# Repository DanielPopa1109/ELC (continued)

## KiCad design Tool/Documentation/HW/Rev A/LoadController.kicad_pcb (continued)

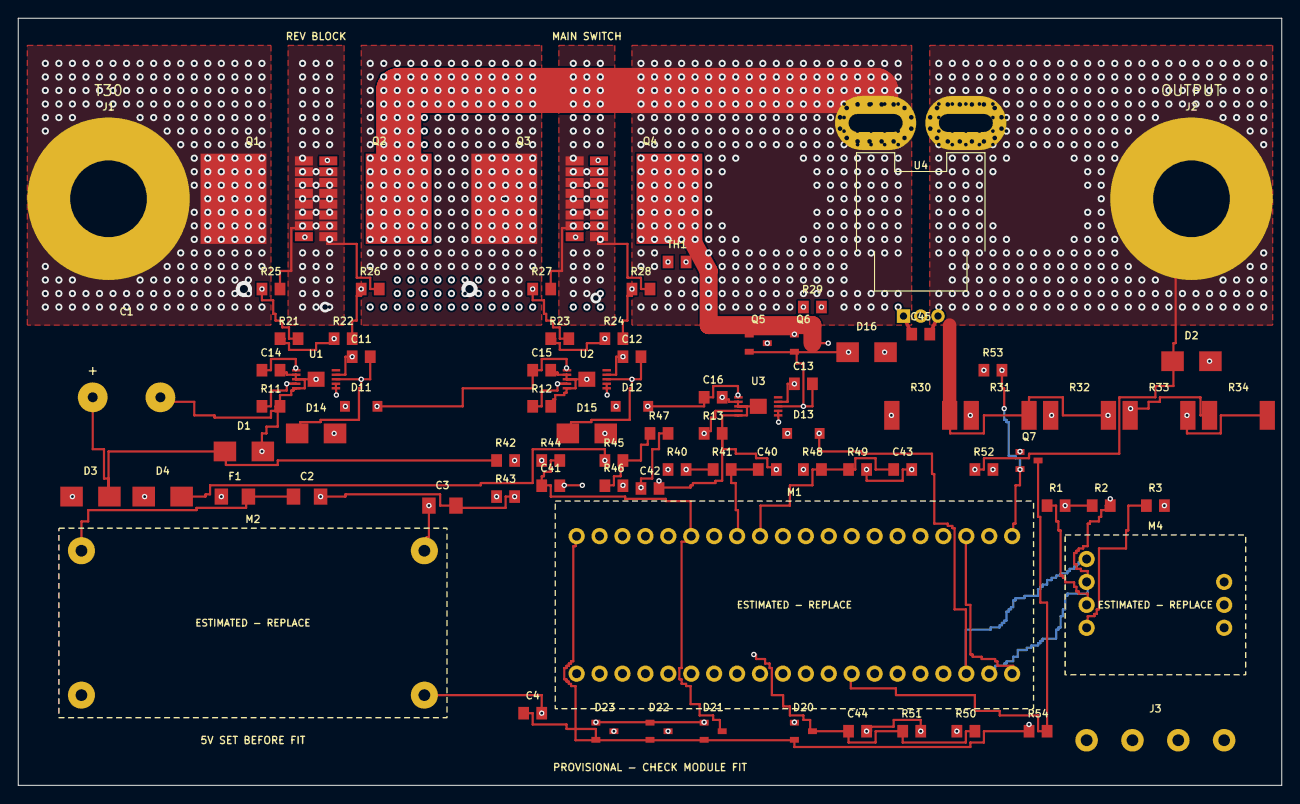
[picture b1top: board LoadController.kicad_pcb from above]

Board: 4 copper layers, 140.0 x 85.0 mm, 84 parts (0 on the bottom side), 41 nets.

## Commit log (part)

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2025-10-20 1 init comm
2025-10-20 2 traces
2025-10-25 3 some changes + traces
2025-11-08 4 osc + traces + fbl updater
2025-11-08 5 change of hw reg iSense
2025-11-09 6 minor changes
2025-11-14 7 updates
2025-11-17 8 Updates in APPL, FBL, Config, DBC
2025-11-18 9 codex tryout
2025-11-18 10 can config up
2025-11-30 11 updates after testing
2025-12-19 12 inb comm
2025-12-19 14 fix commit
2025-12-19 14 codex autosar tryout
2026-01-18 Clean baseline after recovery (no history)
2026-01-18 commit fix
2026-01-18 trace synch
2026-01-19 22 synch traces
2026-01-25 123 456
2026-01-25 comm
2026-01-31 25 cont supp
2026-02-03 26 min max avg
2026-02-10 27 update
2026-03-17 28 resynch logs and some updates
2026-03-21 29 sycnh
2026-03-27 30 resynch + updates
2026-04-05 31 up
2026-04-12 32 up and scripts
2026-04-22 32 upppppp
2026-04-25 last
2026-04-25 cleanup
